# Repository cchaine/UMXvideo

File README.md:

# UMXvideo
A VGA video card capable of displaying text.

## Overview

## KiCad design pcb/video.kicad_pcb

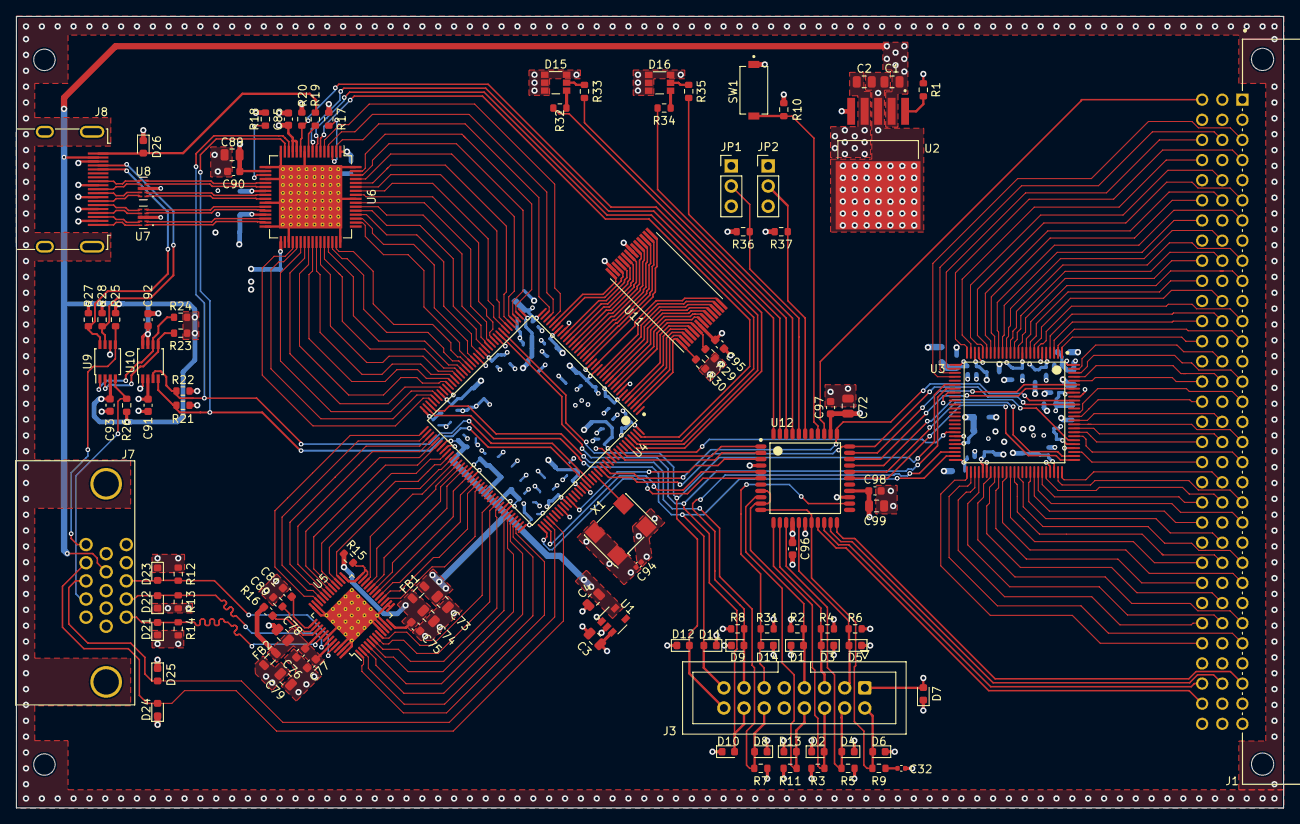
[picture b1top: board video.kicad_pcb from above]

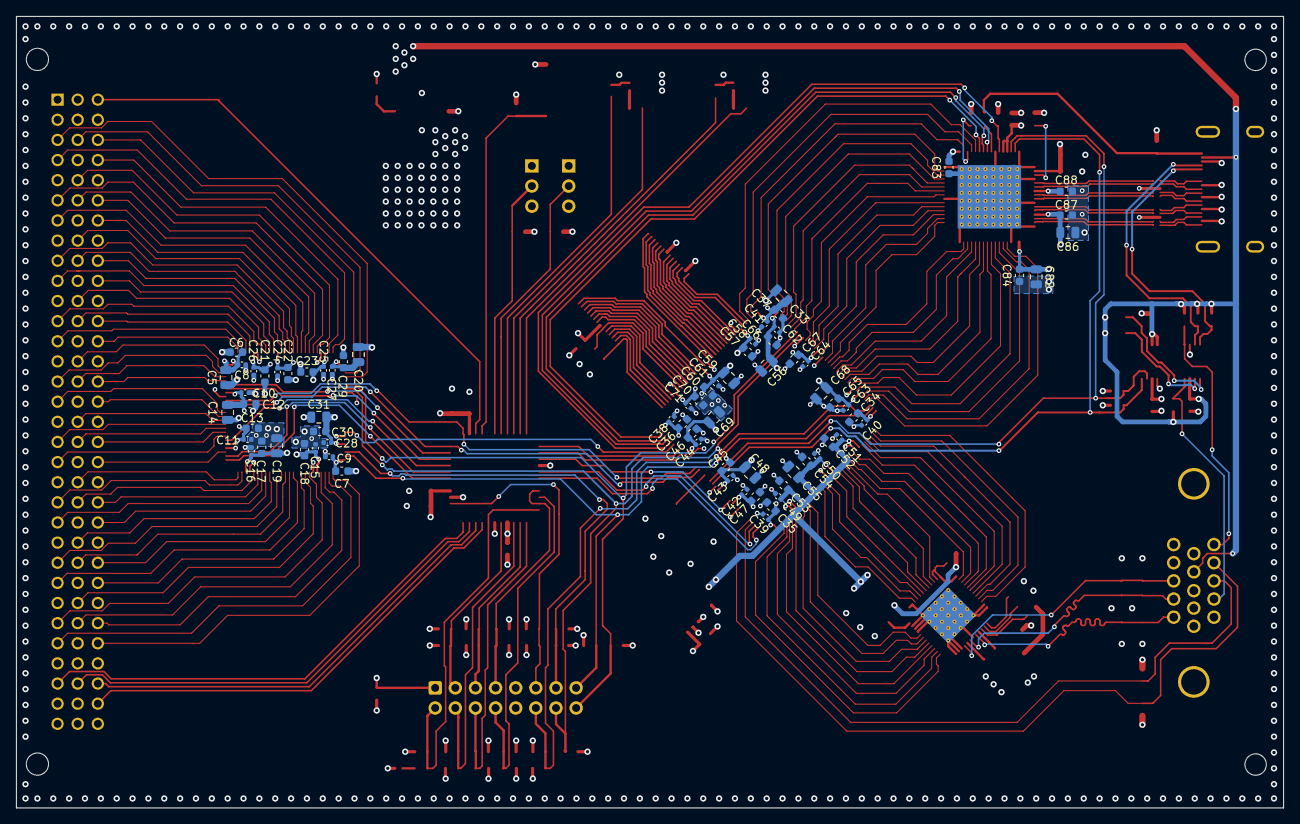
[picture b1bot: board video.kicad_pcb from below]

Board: 4 copper layers, 159.9 x 99.9 mm, 182 parts (72 on the bottom side), 223 nets.

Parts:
C1, C2, C3, C4, C73, C74, C78, C79, C82, C86, C89: 10u; C_0805_2012Metric
C5, C14, C19, C20, C31, C33, C48, C55, C56, C59, C68, C69, C72, C99: 1u; C_0805_2012Metric
C6, C7, C12, C13, C17, C18, C21, C22, C23, C29, C30, C34, C35, C36, C37, C45, C46, C47, C52, C53, C54, C57, C60, C65, C66, C67, C70, C75, C76, C77, C80, C81, C83, C84, C85, C87, C88, C90, C91, C92, C93, C95, C96, C97, C98: 100n; C_0603_1608Metric
C8, C9, C10, C11, C15, C16, C24, C25, C26, C27, C28, C38, C39, C40, C41, C42, C43, C44, C49, C50, C51, C62, C63, C64, C94: 10n; C_0402_1005Metric
C32: 100p; C_0402_1005Metric
C58, C61, C71: 1n; C_0402_1005Metric
D1, D2, D3, D4, D5, D6, D7, D8, D9, D10, D11, D12, D13, D14, D21, D22, D23, D24, D25, D26: D_TVS; D_0603_1608Metric
D15, D16: LED_RGB; CLX6F-FKC-CNP1ST1E1BB7D3D3
FB1, FB2: FerriteBead_Small; L_0805_2012Metric
J1: 09031966921; Harting-09031966921-0-0-0
J3: Conn_02x08_Counter_Clockwise; IDC-Header_2x08_P2.54mm_Vertical
J7: DB15_Female_HighDensity; L77HDE15SD1CH4FVGA
J8: HDMI_A; RAAHD19TR
JP1, JP2: Jumper_3_Open; PinHeader_1x03_P2.54mm_Vertical
MK1, MK3: Mounting_Hole_PAD; MountingHole_2.7mm
R1, R2, R3, R4, R5, R6, R7, R8, R9, R10, R11, R17, R20, R21, R22, R23, R24, R25, R26, R27, R28, R29, R30, R31, R36, R37: 10k; R_0603_1608Metric
R12, R13, R14: 75; R_0603_1608Metric
R15: 2.2k; R_0603_1608Metric
R16: 3.8k; R_0603_1608Metric
R18: 510 @ 1%; R_0603_1608Metric
R19: 1k; R_0603_1608Metric
R32, R34: 60; R_0603_1608Metric
R33, R35: 80; R_0603_1608Metric
SW1: SW_Push; SW_PTS636_SM43J_SMTR_LFS
U1: NCP115; NCP115ASN180T2G
U2: LP3853ESX-3.3/NOPB; LP3853ESX-3_3
U3: LCMXO2-1200HC-4TG100I; Lattice_Semiconductor-LCMXO2-1200HC-4TG100I-Level_C
U4: LCMXO2-7000HC-4TG144C; Lattice_Semiconductor-LCMXO2-7000HC-4TG144C-Level_C
U5: THS8136; TQFP-48-1EP_7x7mm_P0.5mm_EP5x5mm_ThermalVias
U6: TFP410PAP; HTQFP-64-1EP_10x10mm_P0.5mm_EP8x8mm_Mask4.4x4.4mm_ThermalVi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
U7, U8: ESD224DQA; IC_TPD4EUSB30DQAR
U9: PCA9540BDP; TSSOP-8_3x3mm_P0.65mm
U10: NCA9306DPH; TSSOP-8_3x3mm_P0.65mm
U11: S62LV256AL-45TLI; TSOP-I-28_11.8x8mm_P0.55mm
U12: XC9572XL-10VQG44C; Xilinx-XC9572XL-10VQG44C-Level_C
X1: ASV-xxxMHz; Oscillator_SMD_Abracon_ASV-4Pin_7.0x5.1mm

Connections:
+1V8: C4.1, C49.1, C50.1, C51.1, C52.1, C53.1, C54.1, C55.1, C73.1, FB1.1, U1.5 (VOUT), U4.79 (VCCIO1), U4.88 (VCCIO1), U4.102 (VCCIO1)
+3V3: C2.1, C3.1, C5.1, C6.1, C7.1, C8.1, C9.1, C10.1, C11.1, C12.1, C13.1, C14.1, C15.1, C16.1, C17.1, C18.1, C19.1, C20.1, C21.1, C22.1, C23.1, C24.1, C25.1, C26.1, C27.1, C28.1, C29.1, C30.1, C31.1, C33.1, C34.1, C35.1, C36.1, C37.1, C38.1, C39.1, C40.1, C41.1, C42.1, C43.1, C44.1, C45.1, C46.1, C47.1, C48.1, C56.1, C57.1, C58.1, C59.1, C60.1, C61.1, C62.1, C63.1, C64.1, C65.1, C66.1, C67.1, C68.1, C69.1, C70.1, C71.1, C72.1, C79.1, C82.1, C83.1, C84.1, C85.1, C86.1, C87.1, C88.1, C89.1, C90.1, C91.1, C94.1, C95.1, C96.1, C97.1, C98.1, C99.1, D7.2 (A2), FB2.2, J3.1, JP1.3 (B), JP2.3 (B), R2.1, R3.1, R4.1, R5.1, R6.1, R7.1, R8.1, R11.1, R17.1, R18.1, R20.1, R21.1, R22.1, R29.1, R30.1, R31.1, SW1.1, U1.1 (VIN), U1.3 (EN), U2.4 (VOUT), U3.5 (VCCIO3), U3.11 (VCCIO3), U3.23 (VCCIO3), U3.26 (VCCIO2), U3.46 (VCCIO2), U3.50 (VCC), U3.55 (VCCIO1), U3.73 (VCCIO1), U3.80 (VCCIO0), U3.93 (VCCIO0), U3.100 (VCC), U4.7 (VCCIO5), U4.16 (VCCIO4), U4.30 (VCCIO3), U4.36 (VCC), U4.37 (VCCIO2), U4.51 (VCCIO2), U4.66 (VCCIO2), U4.72 (VCC), U4.108 (VCC), U4.118 (VCCIO0), U4.123 (VCCIO0), U4.135 (VCCIO0), U4.144 (VCC), U6.1 (DVDD1), U6.12 (DVDD2), U6.13 (ISEL/~RST), U6.18 (PVDD), U6.23 (TVDD1), U6.29 (TVDD2), U6.33 (DVDD3), U10.2 (refA), U11.28 (VCC), U12.15 (VCCINT), U12.26 (VCCIO), U12.35 (VCCINT), X1.1 (EN), X1.4 (Vdd)
+5V: C1.1, C92.1, C93.1, J1.4, J1.15, J1.20, J1.31, J1.42, J1.47, J1.58, J1.69, J1.74, J1.85, J1.96, J7.9, J8.18 (+5V), R1.2, R23.1, R24.1, R25.1, R26.1, R27.1, R28.1, U2.2 (VIN), U9.3 (VDD), U10.7 (refB), U10.8 (EN)
/HDMI frontend/D0_N: J8.9 (D0-), U8.9 (IO2_S)
/HDMI frontend/D0_P: J8.7 (D0+), U8.10 (IO1_S)
/HDMI frontend/D1_N: J8.6 (D1-), U7.6 (IO4_S)
/HDMI frontend/D1_P: J8.4 (D1+), U7.7 (IO3_S)
/HDMI frontend/D2_N: J8.3 (D2-), U7.9 (IO2_S)
/HDMI frontend/D2_P: J8.1 (D2+), U7.10 (IO1_S)
/HDMI frontend/DC_N: J8.12 (CK-), U8.6 (IO4_S)
/HDMI frontend/DC_P: J8.10 (CK+), U8.7 (IO3_S)
/HDMI frontend/HOTPLUG: R19.1, U6.9 (EDGE/HTPLG)
/HDMI frontend/TX0_N: U6.24 (TX0-), U8.2 (IO2_C)
/HDMI frontend/TX0_P: U6.25 (TX0+), U8.1 (IO1_C)
/HDMI frontend/TX1_N: U6.27 (TX1-), U7.5 (IO4_C)
/HDMI frontend/TX1_P: U6.28 (TX1+), U7.4 (IO3_C)
/HDMI frontend/TX2_N: U6.30 (TX2-), U7.2 (IO2_C)
/HDMI frontend/TX2_P: U6.31 (TX2+), U7.1 (IO1_C)
/HDMI frontend/TXC_N: U6.21 (TXC-), U8.5 (IO4_C)
/HDMI frontend/TXC_P: U6.22 (TXC+), U8.4 (IO3_C)
/Programming interface/BUS_STATUS_GREEN: R34.2, U12.42 (I/O)
/Programming interface/BUS_STATUS_RED: R35.2, U12.41 (I/O)
/Programming interface/COMMON_JTAG_CHAIN: JP1.2 (C), R36.1, U12.40 (I/O)
/Programming interface/JTAG_FROM_BUS: JP2.2 (C), R37.1, U12.39 (I/O)
/Programming interface/VIDEO_STATUS_GREEN: R32.2, U12.44 (I/O,GCK2)
/Programming interface/VIDEO_STATUS_RED: R33.2, U12.43 (I/O,GCK1)
/VGA frontend/AVDD: C76.1, C77.1, C78.1, C80.1, FB2.1, U5.40 (AVDD), U5.44 (AVDD)
/VGA frontend/BLUE: D23.2 (A2), J7.3, R12.1, U5.45 (AB)
/VGA frontend/DVDD: C74.1, C75.1, FB1.2, R15.1, U5.12 (DVDD)
/VGA frontend/GREEN: D22.2 (A2), J7.2, R13.1, U5.43 (AR)
/VGA frontend/RED: D21.2 (A2), J7.1, R14.1, U5.41 (AG)
/Video FPGA/PLLIN: U4.128 (PT18A/PCLKT0_1), X1.3 (OUT)
BUS_CONFIG_DONE: U3.76 (PT17D/DONE), U12.28 (I/O)
BUS_CTRL_CONFIG_SN: D9.2 (A2), J3.13, R8.2, U3.48 (PB20C/SN)
BUS_CTRL_TDI: U3.94 (PT10D/TDI), U12.31 (I/O)
BUS_CTRL_TDI_IN: D5.2 (A2), J3.3, R6.2, U12.16 (I/O)
BUS_CTRL_TDO: U3.95 (PT10C/TDO), U12.32 (I/O)
BUS_CTRL_TDO_IN: D4.2 (A2), J3.4, R5.2, U12.14 (I/O)
BUS_INITB: U3.77 (PT17C/INITN), U12.29 (I/O)
BUS_PROGB: U3.81 (PT15D/PROGRAMN), U12.30 (I/O)
CCK: D12.2 (A2), J3.16, U3.31 (PB6C/MCLK/CCLK), U4.44 (PB12A/MCLK/CCLK)
CONN_0: J1.7, U3.29 (PB6A)
CONN_1: J1.8, U3.28 (PB4D)
CONN_2: J1.9, U3.27 (PB4C/CSSPIN)
CONN_3: J1.10, U3.25 (PL10D)
CONN_4: J1.12, U3.24 (PL10C)
CONN_5: J1.14, U3.21 (PL9B/PCLKC3_0)
CONN_6: J1.16, U3.20 (PL9A/PCLKT3_0)
CONN_7: J1.17, U3.19 (PL8D)
CONN_8: J1.18, U3.18 (PL8C)
CONN_9: J1.19, U3.17 (PL8B)
CONN_10: J1.21, U3.16 (PL8A)
CONN_11: J1.23, U3.15 (PL5D)
CONN_12: J1.25, U3.14 (PL5C)
CONN_13: J1.26, U3.13 (PL5B/PCLKC3_1)
CONN_14: J1.27, U3.12 (PL5A/PCLKT3_1)
CONN_15: J1.28, U3.10 (PL4B)
CONN_16: J1.30, U3.9 (PL4A)
CONN_17: J1.32, U3.8 (PL3D)
CONN_18: J1.34, U3.7 (PL3C)
CONN_19: J1.35, U3.4 (PL3B/PCLKC3_2)
CONN_20: J1.36, U3.3 (PL3A/PCLKT3_2)
CONN_21: J1.37, U3.2 (PL2D/L_GPLLC_IN)
CONN_22: J1.39, U3.1 (PL2C/L_GPLLT_IN)
CONN_23: J1.41, U3.99 (PT9A)
CONN_24: J1.43, U3.98 (PT9B)
CONN_25: J1.44, U3.97 (PT10A)
CONN_26: J1.45, U3.96 (PT10B)
CONN_27: J1.46, U3.88 (PT12A/PCLKT0_1)
CONN_28: J1.48, U3.87 (PT12B/PCLKC0_1)
CONN_29: J1.50, U3.86 (PT12C/SCL/PCLKT0_0)
CONN_30: J1.52, U3.85 (PT12D/SDA/PCLKC0_0)
CONN_31: J1.53, U3.84 (PT15A)
CONN_32: J1.54, U3.83 (PT15B)
CONN_33: J1.55, U3.82 (PT15C/JTAGENB)
CONN_34: J1.57, U3.78 (PT16C)
CONN_35: J1.59, U3.75 (PR2A/(DQ0))
CONN_36: J1.61, U3.74 (PR2B/(DQ0))
CONN_37: J1.62, U3.71 (PR3A/(DQ0))
CONN_38: J1.63, U3.70 (PR3B/(DQ0))
CONN_39: J1.64, U3.69 (PR4A/(DQ0))
CONN_40: J1.66, U3.68 (PR4B/(DQ0))
CONN_41: J1.68, U3.67 (PR4C/(DQ0))
CONN_42: J1.70, U3.64 (PR5B/(DQS0N))
CONN_43: J1.71, U3.63 (PR5C/PCLKT1_0/(DQ0))
CONN_44: J1.72, U3.62 (PR5D/PCLKC1_0/(DQ0))
CONN_45: J1.73, U3.61 (PR8A/(DQS1))
CONN_46: J1.75, U3.59 (PR8D/(DQ1))
CONN_47: J1.77, U3.58 (PR9A/(DQ1))
CONN_48: J1.79, U3.57 (PR9B/(DQ1))
CONN_49: J1.80, U3.54 (PR9C/(DQ1))
CONN_50: J1.81, U3.53 (PR9D/(DQ1))
CONN_51: J1.82, U3.52 (PR10C/(DQ1))
CONN_52: J1.84, U3.51 (PR10D/(DQ1))
DPSRAM_A0: U4.21 (PL15A), U11.10 (A0)
DPSRAM_A1: U4.20 (PL12B/PCLKC4_0), U11.9 (A1)
DPSRAM_A2: U4.19 (PL12A/PCLKT4_0), U11.8 (A2)
DPSRAM_A3: U4.17 (PL11B), U11.7 (A3)
DPSRAM_A4: U4.15 (PL11A), U11.6 (A4)
DPSRAM_A5: U4.14 (PL10B), U11.5 (A5)
DPSRAM_A6: U4.13 (PL10A), U11.4 (A6)
DPSRAM_A7: U4.12 (PL9B), U11.3 (A7)
DPSRAM_A8: U4.5 (PL6A/PCLKT5_0), U11.25 (A8)
DPSRAM_A9: U4.4 (PL4B/L_GPLLC_IN), U11.24 (A9)
DPSRAM_A10: U4.32 (PL24A), U11.21 (A10)
DPSRAM_A11: U4.3 (PL4A/L_GPLLT_IN), U11.23 (A11)
DPSRAM_A12: U4.11 (PL9A), U11.2 (A12)
DPSRAM_A13: U4.6 (PL6B/PCLKC5_0), U11.26 (A13)
DPSRAM_A14: U4.10 (PL8B), U11.1 (A14)
DPSRAM_IO0: U4.22 (PL15B), U11.11 (IO0)
DPSRAM_IO1: U4.23 (PL17A), U11.12 (IO1)
DPSRAM_IO2: U4.24 (PL17B), U11.13 (IO2)
DPSRAM_IO3: U4.25 (PL19A), U11.15 (IO3)
DPSRAM_IO4: U4.26 (PL19B), U11.16 (IO4)
DPSRAM_IO5: U4.27 (PL22A/PCLKT3_0), U11.17 (IO5)
DPSRAM_IO6: U4.28 (PL22B/PCLKC3_0), U11.18 (IO6)
DPSRAM_IO7: U4.31 (PL23D), U11.19 (IO7)
DPSRAM_OE: R30.2, U4.2 (PL3B/L_GPLLC_FB), U11.22 (~OE)
DPSRAM_WE: R29.2, U4.9 (PL8A), U11.27 (~WE)
FPGA_SCL: R22.2, U4.126 (PT22C/SCL/PCLKT0_0), U6.14 (DSEL/SDA), U10.3 (SCLA)
FPGA_SDA: R21.2, U4.125 (PT22D/SDA/PCLKC0_0), U6.15 (BSEL/SCL), U10.4 (SDAA)
GND: C1.2, C2.2, C3.2, C4.2, C5.2, C6.2, C7.2, C8.2, C9.2, C10.2, C11.2, C12.2, C13.2, C14.2, C15.2, C16.2, C17.2, C18.2, C19.2, C20.2, C21.2, C22.2, C23.2, C24.2, C25.2, C26.2, C27.2, C28.2, C29.2, C30.2, C31.2, C32.2, C33.2, C34.2, C35.2, C36.2, C37.2, C38.2, C39.2, C40.2, C41.2, C42.2, C43.2, C44.2, C45.2, C46.2, C47.2, C48.2, C49.2, C50.2, C51.2, C52.2, C53.2, C54.2, C55.2, C56.2, C57.2, C58.2, C59.2, C60.2, C61.2, C62.2, C63.2, C64.2, C65.2, C66.2, C67.2, C68.2, C69.2, C70.2, C71.2, C72.2, C73.2, C74.2, C75.2, C76.2, C77.2, C78.2, C79.2, C81.2, C82.2, C83.2, C84.2, C85.2, C86.2, C87.2, C88.2, C89.2, C90.2, C91.2, C92.2, C93.2, C94.2, C95.2, C96.2, C97.2, C98.2, C99.2, D1.1 (A1), D2.1 (A1), D3.1 (A1), D4.1 (A1), D5.1 (A1), D6.1 (A1), D7.1 (A1), D8.1 (A1), D9.1 (A1), D10.1 (A1), D11.1 (A1), D12.1 (A1), D13.1 (A1), D14.1 (A1), D15.1 (RK), D15.2 (GK), D15.3 (BK), D15.6 (RA), D16.1 (RK), D16.2 (GK), D16.3 (BK), D16.6 (RA), D21.1 (A1), D22.1 (A1), D23.1 (A1), D24.1 (A1), D25.1 (A1), D26.1 (A1), J1.2, J1.5, J1.6, J1.11, J1.13, J1.22, J1.24, J1.29, J1.33, J1.38, J1.40, J1.49, J1.51, J1.56, J1.60, J1.65, J1.67, J1.76, J1.78, J1.83, J1.86, J1.87, J1.91, J1.92, J1.94, J1.95, J3.9, J3.10, J7.5, J7.6, J7.7, J7.8, J7.10, J8.2 (D2S), J8.5 (D1S), J8.8 (D0S), J8.11 (CKS), J8.17 (GND), JP1.1 (A), JP2.1 (A), R10.2, R12.2, R13.2, R14.2, R16.2, R36.2, R37.2, U1.2 (GND), U2.3 (GND), U2.5 (~ERROR), U2.6 (GND), U3.6 (GND), U3.22 (GND), U3.33 (GND), U3.44 (GND), U3.56 (GND), U3.72 (GND), U3.79 (GND), U3.92 (GND), U4.8 (GND), U4.18 (GND), U4.29 (GND), U4.46 (GND), U4.53 (GND), U4.64 (GND), U4.80 (GND), U4.90 (GND), U4.101 (GND), U4.116 (GND), U4.124 (GND), U4.134 (GND), U5.9 (B1), U5.10 (B0), U5.11 (DVSS), U5.13 (R0), U5.14 (R1), U5.35 (G1), U5.36 (G0), U5.42 (AVSS), U5.46 (AVSS), U5.47 (M1), U5.48 (M2), U5.49 (EP), U6.10 (~PD), U6.16 (DGND1), U6.17 (PGND), U6.20 (TGND1), U6.26 (TGND2), U6.32 (TGND3), U6.35 (DKEN), U6.48 (DGND2), U6.56 (IDCK-), U6.64 (DGND3), U6.65 (EP), U7.3 (GND), U7.8 (GND), U8.3 (GND), U8.8 (GND), U9.6 (VSS), U10.1 (GND), U11.14 (GND), U11.20 (~CE), U12.4 (GND), U12.17 (GND), U12.25 (GND), X1.2 (GND)
HDMI_CLK: U4.47 (PB13A), U6.57 (IDCK+)
HDMI_D0: U4.38 (PB4A), U6.63 (DATA0)
HDMI_D1: U4.39 (PB4B), U6.62 (DATA1)
HDMI_D2: U4.40 (PB6A/CSSPIN), U6.61 (DATA2)
HDMI_D3: U4.41 (PB6B), U6.60 (DATA3)
HDMI_D4: U4.42 (PB9A), U6.59 (DATA4)
HDMI_D5: U4.43 (PB9B), U6.58 (DATA5)
HDMI_D6: U4.48 (PB13B), U6.55 (DATA6)
HDMI_D7: U4.49 (PB16A/PCLKT2_0), U6.54 (DATA7)
HDMI_D8: U4.50 (PB16B/PCLKC2_0), U6.53 (DATA8)
HDMI_D9: U4.52 (PB18A), U6.52 (DATA9)
HDMI_D10: U4.54 (PB18B), U6.51 (DATA10)
HDMI_D11: U4.55 (PB23A/PCLKT2_1), U6.50 (DATA11)
HDMI_D12: U4.56 (PB23B/PCLKC2_1), U6.47 (DATA12)
HDMI_D13: U4.57 (PB26A), U6.46 (DATA13)
HDMI_D14: U4.58 (PB26B), U6.45 (DATA14)
HDMI_D15: U4.59 (PB29A), U6.44 (DATA15)
HDMI_D16: U4.60 (PB29B), U6.43 (DATA16)
HDMI_D17: U4.61 (PB31A), U6.42 (DATA17)
HDMI_D18: U4.62 (PB31B), U6.41 (DATA18)
HDMI_D19: U4.63 (PB31D), U6.40 (DATA19)
HDMI_D20: U4.65 (PB35A), U6.39 (DATA20)
HDMI_D21: U4.67 (PB35B), U6.38 (DATA21)
HDMI_D22: U4.68 (PB37A), U6.37 (DATA22)
HDMI_D23: U4.69 (PB37B), U6.36 (DATA23)
HDMI_DDC_SCL: J8.15 (SCL), R27.2, U9.8 (SC1)
HDMI_DDC_SDA: J8.16 (SDA), R28.2, U9.7 (SD1)
HDMI_DE: U4.35 (PL25B), U6.2 (DE)
HDMI_HSYNC: U4.34 (PL25A), U6.4 (HSYNC)
HDMI_I2C_A1: U4.141 (PT10A), U6.8 (CTL1/A1/DK1)
HDMI_I2C_A2: U4.142 (PT9B), U6.7 (CTL2/A2/DK2)
HDMI_I2C_A3: U4.143 (PT9A), U6.6 (CTL3/A3/DK3)
HDMI_SENSE: R20.2, U4.140 (PT10B), U6.11 (MSEN/PO1)
HDMI_VSYNC: U4.33 (PL24B), U6.5 (VSYNC)
JTAG_TCK: U3.91 (PT11C/TCK/TEST_CLK), U4.131 (PT17C/TCK/TEST_CLK), U12.34 (I/O,GTS2)
JTAG_TCK_IN: D6.2 (A2), J3.2, R9.1, U12.11 (TCK), U12.18 (I/O)
JTAG_TMS: U3.90 (PT11D/TMS), U4.130 (PT17D/TMS), U12.33 (I/O,GSR)
JTAG_TMS_IN: D1.2 (A2), J3.7, R2.2, U12.8 (I/O), U12.10 (TMS)
MISO: D10.2 (A2), J3.14, U3.32 (PB6D/SO/SPISO), U4.45 (PB12B/SO/SPISO)
MOSI: D11.2 (A2), J3.15, U3.49 (PB20D/SI/SISPI), U4.71 (PB38B/SI/SISPI)
unnamed: C32.1, R9.2
unnamed: D15.4 (BA), R32.1
unnamed: D15.5 (GA), R33.1
unnamed: D16.4 (BA), R34.1
unnamed: D16.5 (GA), R35.1
unnamed: D26.2 (A2), J8.19 (HPD), R19.2
unnamed: R1.1, U2.1 (~SD)
unnamed: C80.2, U5.39 (COMP)
unnamed: R16.1, U5.38 (FSADJ)
unnamed: R15.2, U5.23 (~BLANK), U5.24 (~SYNC), U5.25 (SYNC_T)
unnamed: C81.1, U5.37 (VREF)
unnamed: R18.2, U6.19 (TFADJ)
unnamed: R17.2, U6.3 (VREF)
unnamed: R24.2, U9.1 (SCL), U10.6 (SCLB)
unnamed: R23.2, U9.2 (SDA), U10.5 (SDAB)
PROG_CTRL_TDI: D13.2 (A2), J3.8, R11.2, U12.9 (TDI)
PROG_CTRL_TDO: D14.2 (A2), J3.11, R31.2, U12.24 (TDO)
RESET: R10.1, SW1.2, U12.37 (I/O)
RESET_CONN: J1.3, U12.36 (I/O,GTS1)
TCK_CONN: J1.89, U12.21 (I/O)
TDI_CONN: J1.90, U12.20 (I/O)
TDO_CONN: J1.93, U12.19 (I/O)
TMS_CONN: J1.88, U12.22 (I/O)
VGA_B0: U4.98 (PR7A/(DQ0)), U5.8 (B2)
VGA_B1: U4.99 (PR5B/(DQ0)), U5.7 (B3)
VGA_B2: U4.100 (PR5A/(DQ0)), U5.6 (B4)
VGA_B3: U4.103 (PR4C), U5.5 (B5)
VGA_B4: U4.104 (PR3B/R_GPLLC_IN/(DQ0)), U5.4 (B6)
VGA_B5: U4.105 (PR3A/R_GPLLT_IN/(DQ0)), U5.3 (B7)
VGA_B6: U4.106 (PR2B/R_GPLLC_FB/(DQ0)), U5.2 (B8)
VGA_B7: U4.107 (PR2A/R_GPLLT_FB/(DQ0)), U5.1 (B9)
VGA_CLK: U4.83 (PR17B/(DQ1)), U5.26 (CLK)
VGA_DDC_SCL: J7.15, R25.2, U9.5 (SC0)
VGA_DDC_SDA: J7.12, R26.2, U9.4 (SD0)
VGA_G0: U4.73 (PR24B/(DQ1)), U5.34 (G2)
VGA_G1: U4.74 (PR24A/(DQ1)), U5.33 (G3)
VGA_G2: U4.75 (PR23B/(DQ1)), U5.32 (G4)
VGA_G3: U4.76 (PR23A/(DQ1)), U5.31 (G5)
VGA_G4: U4.77 (PR21B/(DQ1)), U5.30 (G6)
VGA_G5: U4.78 (PR21A/(DQ1)), U5.29 (G7)
VGA_G6: U4.81 (PR18B/(DQ1)), U5.28 (G8)
VGA_G7: U4.82 (PR18A/(DQ1)), U5.27 (G9)
VGA_HSYNC: D25.2 (A2), J7.13, U4.111 (PT35B)
VGA_R0: U4.93 (PR11B/(DQS0N)), U5.15 (R2)
VGA_R1: U4.92 (PR12A/PCLKT1_0/(DQ0)), U5.16 (R3)
VGA_R2: U4.91 (PR12B/PCLKC1_0/(DQ0)), U5.17 (R4)
VGA_R3: U4.89 (PR15A), U5.18 (R5)
VGA_R4: U4.87 (PR15B), U5.19 (R6)
VGA_R5: U4.86 (PR16A/(DQS1)), U5.20 (R7)
VGA_R6: U4.85 (PR16B/(DQS1N)), U5.21 (R8)
VGA_R7: U4.84 (PR17A/(DQ1)), U5.22 (R9)
VGA_VSYNC: D24.2 (A2), J7.14, U4.112 (PT35A)
VIDEO_CONFIG_DONE: U4.109 (PT36D/DONE), U12.6 (I/O)
VIDEO_CTRL_CONFIG_SN: D8.2 (A2), J3.12, R7.2, U4.70 (PB38A/SN)
VIDEO_CTRL_TDI: U4.136 (PT14D/TDI), U12.2 (I/O)
VIDEO_CTRL_TDI_IN: D3.2 (A2), J3.5, R4.2, U12.13 (I/O)
VIDEO_CTRL_TDO: U4.137 (PT14C/TDO), U12.1 (I/O,GCK3)
VIDEO_CTRL_TDO_IN: D2.2 (A2), J3.6, R3.2, U12.12 (I/O)
VIDEO_INITB: U4.110 (PT36C/INITN), U12.5 (I/O)
VIDEO_PROGB: U4.119 (PT27D/PROGRAMN), U12.3 (I/O)
VIDEO_SPI_CS: U3.43 (PB18B), U4.139 (PT11A)

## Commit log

2022-02-21 add base board
2022-02-22 add two fpgas
2022-02-24 add more components
2022-02-25 change lcmxo2-4000hc for lcmxo2-7000hc to have enough ebr for 1080p text mode
2022-02-26 add architecture diagramé
2022-02-26 fix wrong vga connector logo
2022-02-26 add jtag and spi tag connect to the bus fpga
2022-02-26 add connector labels
2022-02-27 add bypass to the video controller
2022-02-27 add jtag signals to the video controller
2022-02-27 add ths8136 symbol
2022-02-28 add vga frontend
2022-02-28 fix wrong fasdj resistor on vga frontend
2022-02-28 start adding decoupling caps for the hdmi frontend
2022-02-28 start adding schematic for the hdmi frontend
2022-03-01 add hdmi frontend
2022-03-01 add i2c mux for ddc
2022-03-01 add global symbals to the video controller
2022-03-02 add esd protection for the hdmi frontend
2022-03-02 moved i2c mux to another page
2022-03-02 choose components and add footprints
2022-03-02 add video controller oscillator
2022-03-02 add decoupling caps on bus controller
2022-03-03 place bypass caps
2022-03-03 move bypass caps on the bottom
2022-03-05 place components around connectors
2022-03-05 placed all components
2022-03-09 add traces from bus to bus controller
2022-03-20 add traces for hdmi interface with proper anti crosstalk
2022-03-20 add via stitching near hdmi parallel bus vias
2022-03-20 change the bank for the hdmi interface
2022-03-20 add traces to the vga interface minimizing crosstalk
2022-03-20 add traces for the bus with crosstalk reduction
2022-03-20 add dualport ram for debug purposes
2022-03-21 route sram
2022-03-21 add length matching to parallel buses
2022-03-22 fan out the spi lines from the video fpga
2022-03-22 add a unified programming connector
2022-03-26 add traces to the vga frontend
2022-03-26 add traces for the hdmi frontend
2022-03-27 undo the trace length matching for the vga frontend
2022-03-28 add the 3v3 voltage regulator
2022-04-03 add the programming controller
2022-04-03 add the programming controller's jtag to the connector
2022-04-15 add shield
2022-04-15 finish routing essential programming nets
2022-04-15 add status led in the programming interface schematic
2022-04-16 add rgb led status
2022-04-18 add status leds and jtag chain jumpers
2022-04-18 start routing power
2022-04-18 add hdmi sense to video controller
2022-04-22 finish routing power, need to fix bus interface controller
2022-04-24 start fixing the bus connection
2022-04-24 reroute signals from conntector to controller
2022-04-25 passed erc and drc
2022-04-27 finished the board
2022-04-27 start adding silkscreen
2022-05-28 fix missing lcmx02
